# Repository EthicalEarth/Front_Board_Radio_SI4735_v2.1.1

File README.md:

# Front_Board_Radio_SI4735_v2.1.1
New version of Front Board v2.1.1 for Radio SI4735 v2.1.1.

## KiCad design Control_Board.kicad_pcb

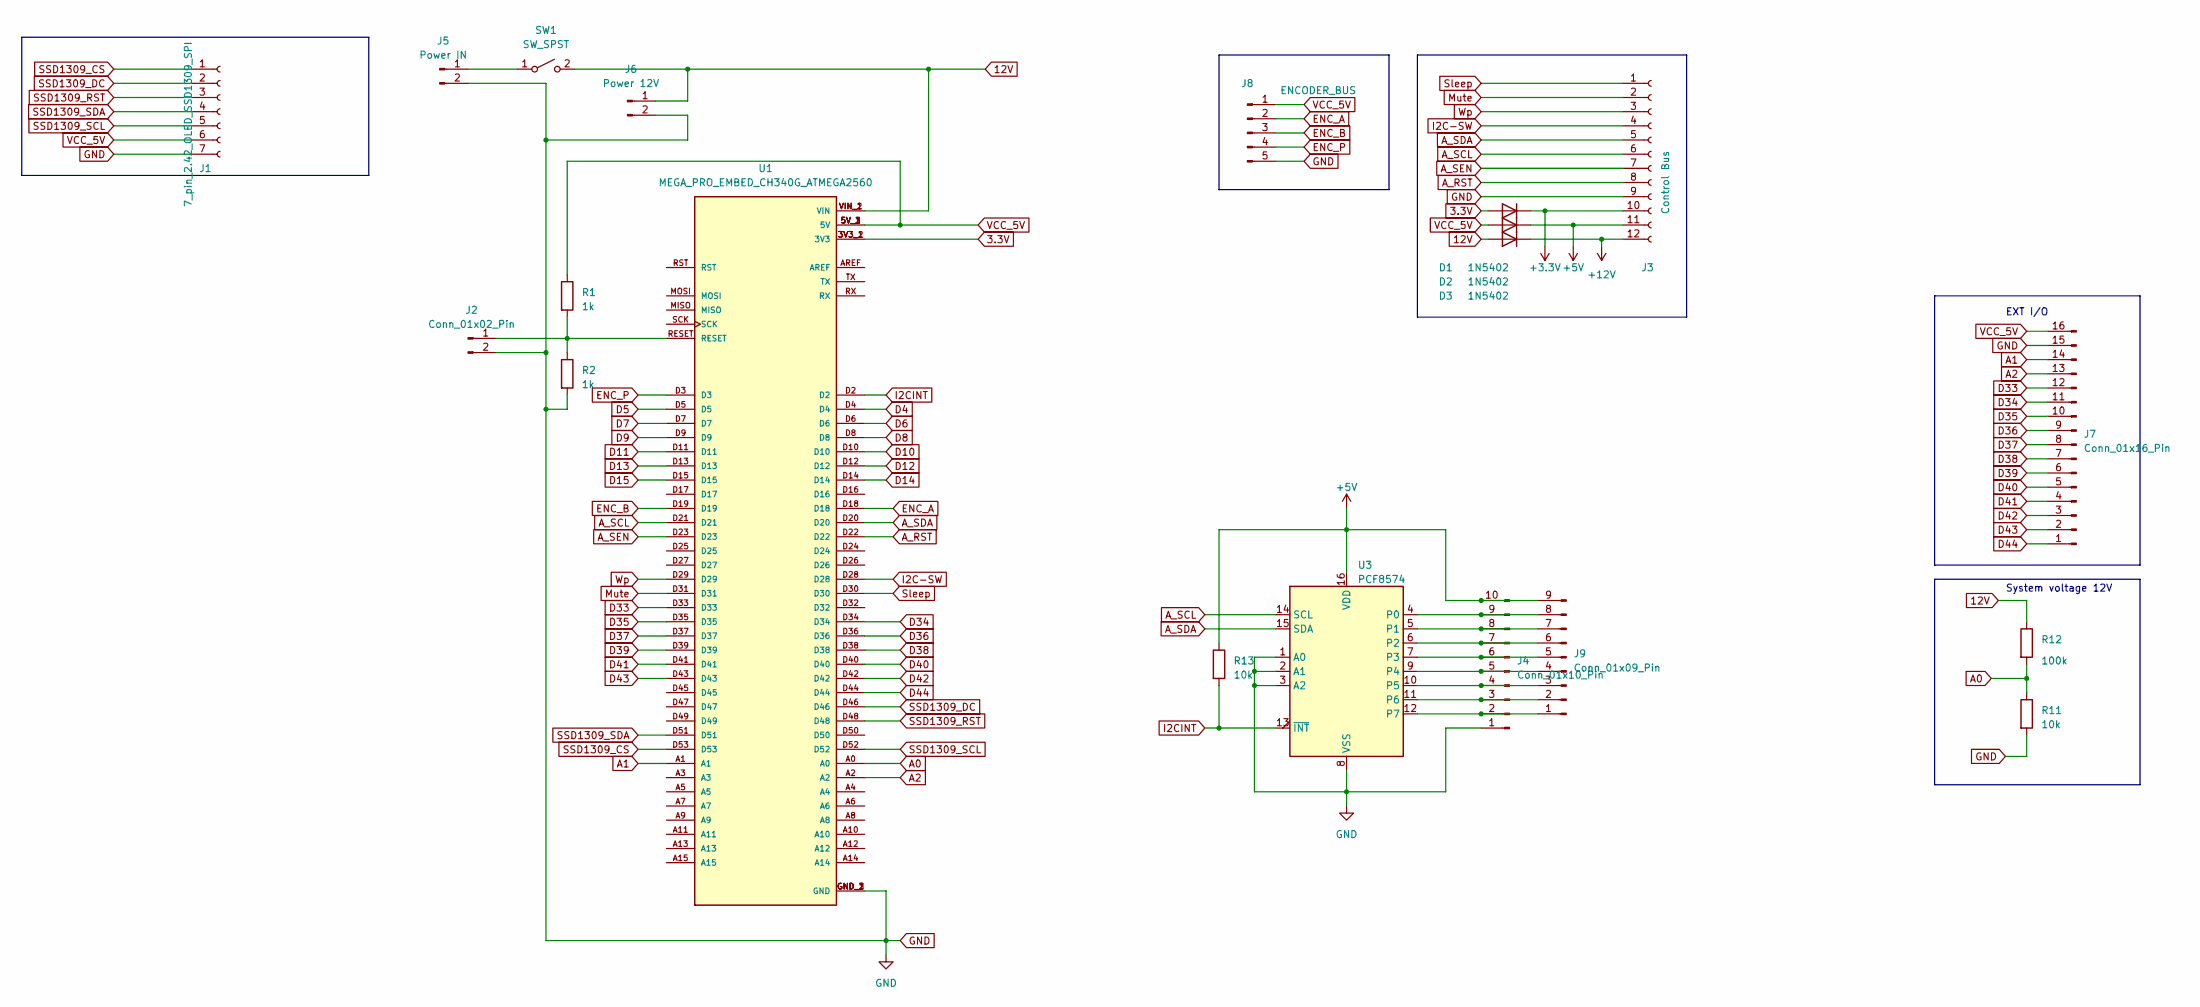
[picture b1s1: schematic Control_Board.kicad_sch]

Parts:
D1, D2, D3: 1N5402; D_1206_3216Metric
J1: 7_pin_2.42_OLED_SSD1309_SPI; PinSocket_1x07_P2.54mm_Vertical
J2: Conn_01x02_Pin; PinHeader_1x02_P1.27mm_Vertical
J3: Control Bus; PinSocket_1x12_P2.54mm_Vertical
J4: Conn_01x10_Pin; PinSocket_1x10_P1.27mm_Vertical
J5: Power IN; PinSocket_1x02_P2.54mm_Vertical
J6: Power 12V; PinSocket_1x02_P2.54mm_Vertical
J7: Conn_01x16_Pin; PinHeader_1x16_P2.54mm_Vertical
J8: ENCODER_BUS; PinHeader_1x05_P2.54mm_Vertical
J9: Conn_01x09_Pin; PinHeader_1x09_P2.54mm_Vertical
R1, R2: 1k; R_1206_3216Metric
R11, R13: 10k; R_1206_3216Metric
R12: 100k; R_1206_3216Metric
SW1: SW_SPST; PinSocket_1x02_P2.54mm_Vertical
U1: MEGA_PRO_EMBED_CH340G_ATMEGA2560; MODULE_MEGA_PRO_EMBED_CH340G_ATMEGA2560; PARTREV 12/May/2017
U3: PCF8574; DIP-16_W7.62mm

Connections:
3.3V: D1.2 (A), U1.3V3_1 (3V3), U1.3V3_2 (3V3)
12V: D2.2 (A), J6.1, R12.1, SW1.2 (B), U1.VIN_1 (VIN), U1.VIN_2 (VIN)
+3V3: D1.1 (K), J3.10
+5V: D3.1 (K), J3.11, J4.10, J9.9, R13.1, U3.16 (VDD)
+12V: D2.1 (K), J3.12
A0: R11.1, R12.2, U1.A0
A1: J7.14, U1.A1
A2: J7.13, U1.A2
A_RST: J3.8, U1.D22
A_SCL: J3.6, U1.D21, U3.14 (SCL)
A_SDA: J3.5, U1.D20, U3.15 (SDA)
A_SEN: J3.7, U1.D23
D4: U1.D4
D5: U1.D5
D6: U1.D6
D7: U1.D7
D8: U1.D8
D9: U1.D9
D10: U1.D10
D11: U1.D11
D12: U1.D12
D13: U1.D13
D14: U1.D14
D15: U1.D15
D33: J7.12, U1.D33
D34: J7.11, U1.D34
D35: J7.10, U1.D35
D36: J7.9, U1.D36
D37: J7.8, U1.D37
D38: J7.7, U1.D38
D39: J7.6, U1.D39
D40: J7.5, U1.D40
D41: J7.4, U1.D41
D42: J7.3, U1.D42
D43: J7.2, U1.D43
D44: J7.1, U1.D44
ENC_A: J8.2, U1.D18
ENC_B: J8.3, U1.D19
ENC_P: J8.4, U1.D3
GND: J1.7, J2.2, J3.9, J4.1, J5.2, J6.2, J7.15, J8.5, R2.2, R11.2, U1.GND_1 (GND), U1.GND_2 (GND), U1.GND_3 (GND), U3.1 (A0), U3.2 (A1), U3.3 (A2), U3.8 (VSS)
I2C-SW: J3.4, U1.D28
I2CINT: R13.2, U1.D2, U3.13 (~INT)
Mute: J3.2, U1.D31
unnamed: J2.1, R1.2, R2.1, U1.RESET
unnamed: J4.2, J9.1, U3.12 (P7)
unnamed: J4.3, J9.2, U3.11 (P6)
unnamed: J4.4, J9.3, U3.10 (P5)
unnamed: J4.5, J9.4, U3.9 (P4)
unnamed: J4.6, J9.5, U3.7 (P3)
unnamed: J4.7, J9.6, U3.6 (P2)
unnamed: J4.8, J9.7, U3.5 (P1)
unnamed: J4.9, J9.8, U3.4 (P0)
unnamed: J5.1, SW1.1 (A)
SSD1309_CS: J1.1, U1.D53
SSD1309_DC: J1.2, U1.D46
SSD1309_RST: J1.3, U1.D48
SSD1309_SCL: J1.5, U1.D52
SSD1309_SDA: J1.4, U1.D51
Sleep: J3.1, U1.D30
VCC_5V: D3.2 (A), J1.6, J7.16, J8.1, R1.1, U1.5V_1 (5V), U1.5V_2 (5V), U1.5V_3 (5V)
Wp: J3.3, U1.D29

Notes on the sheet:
System voltage 12V
EXT I/O

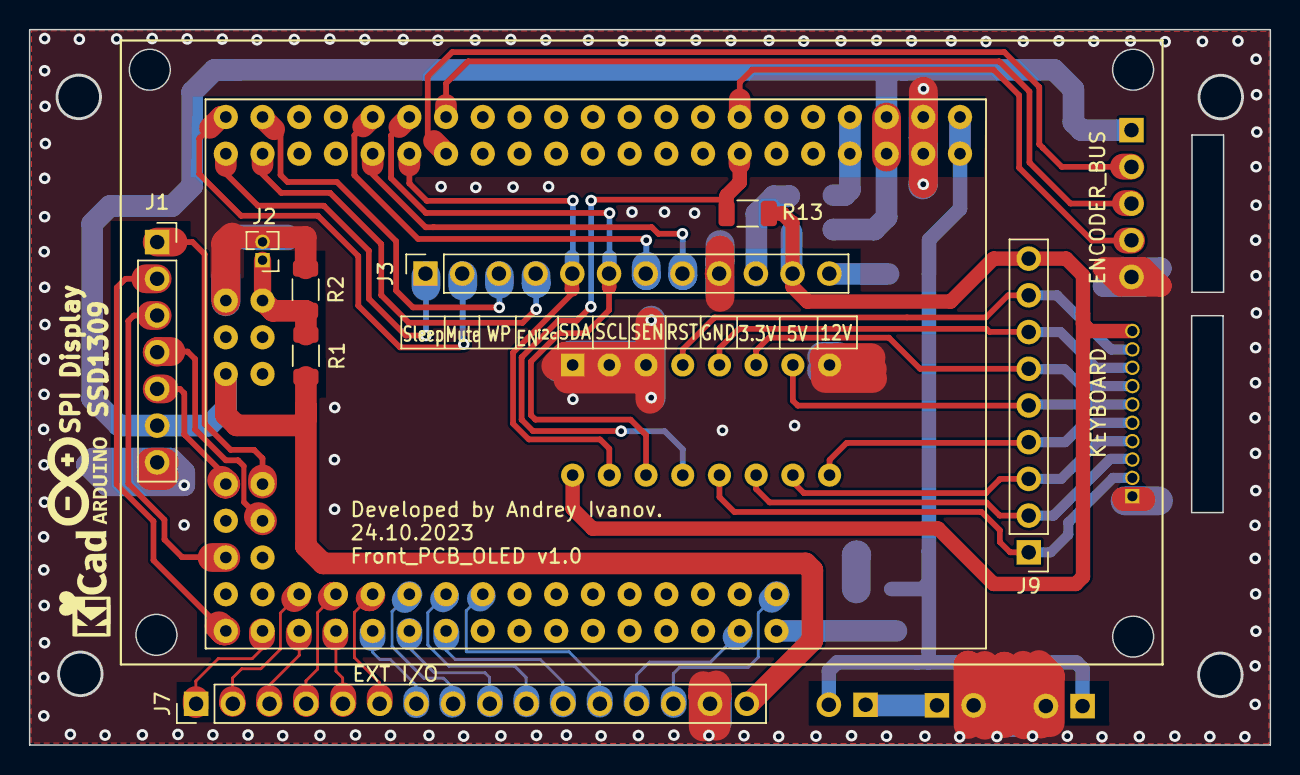
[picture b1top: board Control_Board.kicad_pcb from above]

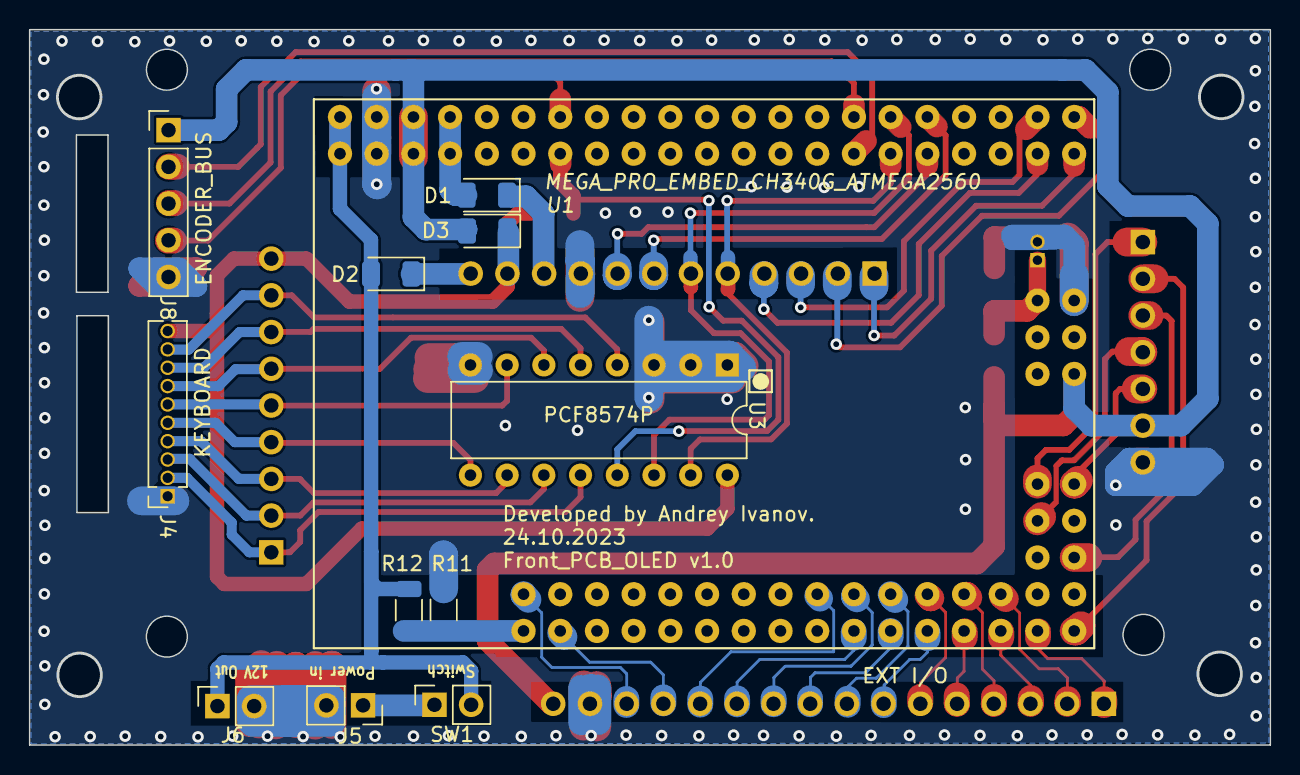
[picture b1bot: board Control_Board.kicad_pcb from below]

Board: 2 copper layers, 85.8 x 49.5 mm, 20 parts (11 on the bottom side), 49 nets.

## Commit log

2023-11-05 Init
2023-11-10 Changes.
